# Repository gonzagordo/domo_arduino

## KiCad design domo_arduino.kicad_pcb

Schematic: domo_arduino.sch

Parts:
C1: C; footrint_condensador_3
C2: CP; footprint_condensador_micro
D1: DIODE; footprint_comp_ver_2
D2, D3, D4, D6, D7: LED; footprint_led_3mm
IC1, IC2, IC3, IC4, IC5: MOC3041M; footprint_dip_6
P1: CONN_6; footprint_conector_6
P2, P3, P4, P5, P6, P7, P8: CONN_2; footprint_conector_2
R1, R2, R3, R4, R5, R6, R7, R8, R9, R10, R11, R12, R13, R14, R15: R; footprint_comp_hor_5
U1: 78L05; footprint_7805_vert
U2, U3, U4, U7, U8: TRIAC; footprint_BTA_vert
U5: ARDUINO_MINI; footprint_arduino
U6: NRF24L01+; footprint_nrf24l01
sil1: SIL_7; footprint_SIL-7

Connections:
+3.3V: C1.1, C2.1, U5.2, U6.2
CE: U5.26, U6.3
CSN: U5.25, U6.4
E1: P1.1, U5.20, sil1.3
E2: P1.2, U5.21, sil1.4
E3: P1.3, U5.22, sil1.5
E4: P1.4, U5.23, sil1.6
E5: P1.5, U5.24, sil1.7
GND: C1.2, C2.2, D2.2 (K), D3.2 (K), D4.2 (K), D6.2 (K), D7.2 (K), IC1.2, IC2.2, IC3.2, IC4.2, IC5.2, P1.6, P3.1, U1.GND, U5.14, U5.19, U6.1
L: P2.2, U2.1, U3.1, U4.1, U7.1, U8.1
N: P2.1, P4.2, P5.2, P6.2, P7.2, P8.2
unnamed: D2.1 (A), R11.2
unnamed: R9.2, U7.3
unnamed: IC4.6, R9.1
unnamed: IC4.1, R7.2
unnamed: IC4.4, P7.1, U7.2
unnamed: IC5.1, R8.2
unnamed: R10.2, U8.3
unnamed: IC5.6, R10.1
unnamed: D3.1 (A), R12.2
unnamed: IC5.4, P8.1, U8.2
unnamed: D6.1 (A), R14.2
unnamed: D7.1 (A), R15.2
unnamed: D4.1 (A), R13.2
unnamed: D1.2 (K), U1.VI
unnamed: IC3.6, R6.1
unnamed: IC3.1, R3.2
unnamed: R5.2, U3.3
unnamed: IC2.6, R5.1
unnamed: IC2.1, R2.2
unnamed: R6.2, U4.3
unnamed: IC3.4, P6.1, U4.2
unnamed: IC1.6, R4.1
unnamed: IC1.1, R1.2
unnamed: R4.2, U2.3
unnamed: IC1.4, P4.1, U2.2
unnamed: IC2.4, P5.1, U3.2
S1: R1.1, R15.1, U5.8
S2: R2.1, R14.1, U5.7
S3: R3.1, R13.1, U5.6
S4: R7.1, R12.1, U5.5
S5: R8.1, R11.1, U5.4
miso: U5.30, U6.7
mosi: U5.29, U6.6
sck: U5.1, U6.5

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
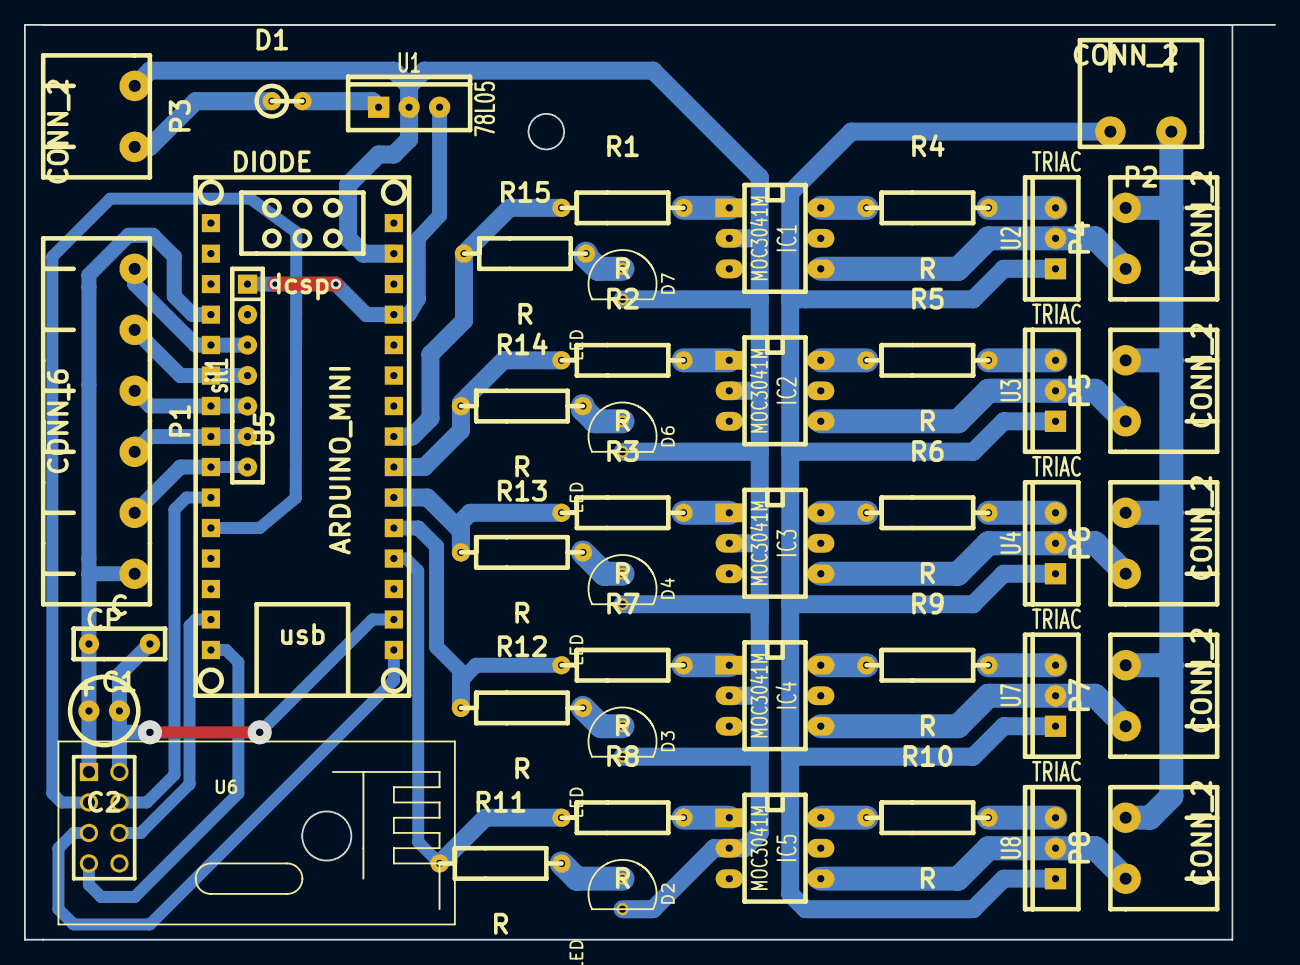
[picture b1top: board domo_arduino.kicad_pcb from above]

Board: 2 copper layers, 104.1 x 76.2 mm, 45 parts (0 on the bottom side), 47 nets.

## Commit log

2017-08-13 circuito basico con arduino, funcional mejorable ya hay uno funcionando en proyector y el maestro
